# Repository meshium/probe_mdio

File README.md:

The PROBE_MDIO project

This is the PROBE_MDIO, an essential hardware multitool for exploring the MMI bus.

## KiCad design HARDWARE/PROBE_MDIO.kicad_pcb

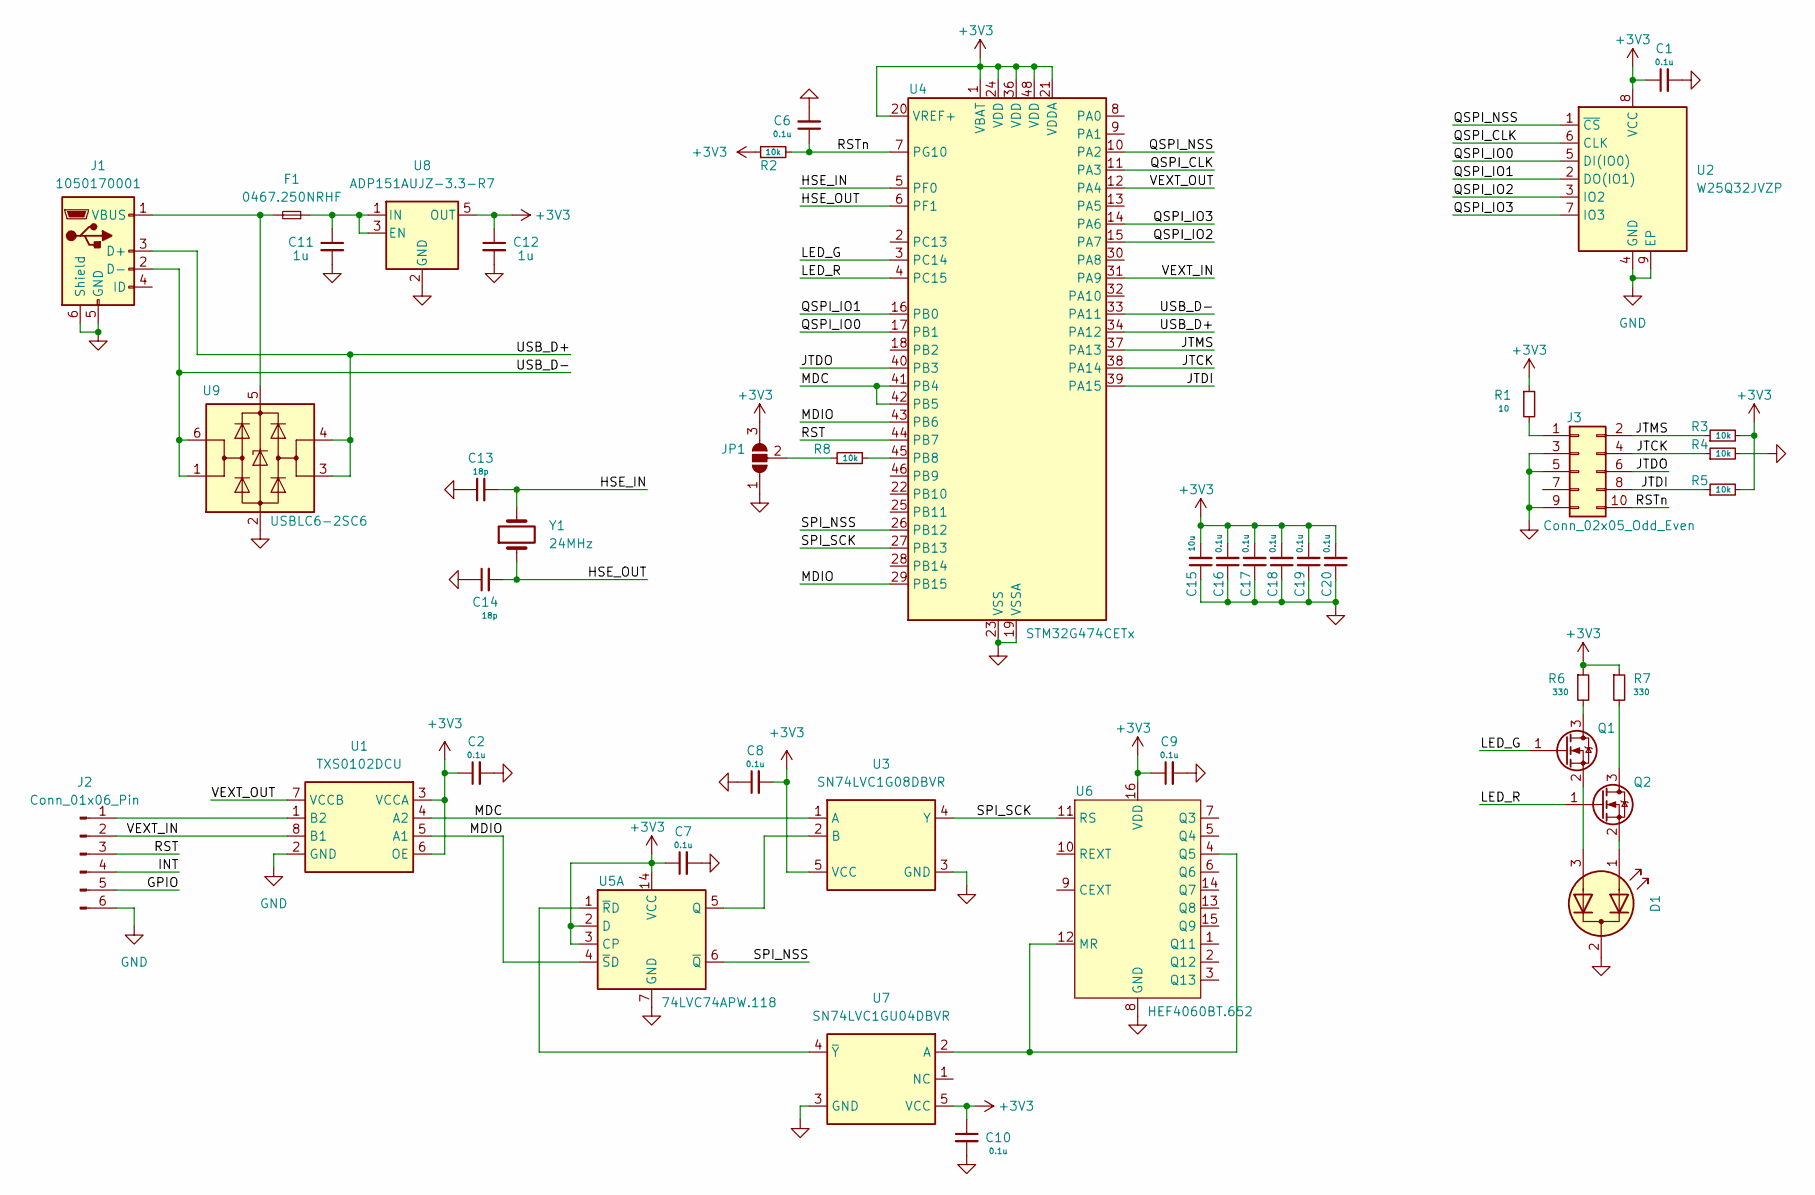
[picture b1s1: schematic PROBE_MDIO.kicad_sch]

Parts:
C1, C2, C6, C7, C8, C9, C10, C16, C17, C18, C19, C20: 0.1u; C_0402_1005Metric
C11, C12: 1u; C_0402_1005Metric
C13, C14: 18p; C_0402_1005Metric
C15: 10u; C_0603_1608Metric
D1: LED_Dual_AAK; LED_D3.0mm-3
F1: 0467.250NRHF; Fuse_0603_1608Metric
J1: 1050170001; USB_Micro-B_Molex-105017-0001
J2: Conn_01x06_Pin; PinHeader_1x06_P2.54mm_Horizontal
J3: Conn_02x05_Odd_Even; PinHeader_2x05_P1.27mm_Vertical
JP1: SolderJumper_3_Open; SolderJumper-3_P2.0mm_Open_TrianglePad1.0x1.5mm_NumberLabels
Q1, Q2: 2N7002; SOT-23
R1: 10; R_0402_1005Metric
R2, R3, R4, R5, R8: 10k; R_0402_1005Metric
R6, R7: 330; R_0402_1005Metric
U1: TXS0102DCU; VSSOP-8_2.3x2mm_P0.5mm
U2: W25Q32JVZP; WSON-8-1EP_6x5mm_P1.27mm_EP3.4x4.3mm
U3: SN74LVC1G08DBVR; SOT-23-5
U4: STM32G474CETx; LQFP-48_7x7mm_P0.5mm
U5: 74LVC74APW.118; TSSOP-14_4.4x5mm_P0.65mm
U6: HEF4060BT.652; SO-16_3.9x9.9mm_P1.27mm
U7: SN74LVC1GU04DBVR; SOT-23-5
U8: ADP151AUJZ-3.3-R7; TSOT-23-5
U9: USBLC6-2SC6; SOT-23-6
Y1: 24MHz; Crystal_SMD_3225-4Pin_3.2x2.5mm

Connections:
+3V3: C1.1, C2.1, C7.1, C8.2, C9.1, C10.1, C12.1, C15.2, C16.2, C17.2, C18.2, C19.2, C20.2, JP1.3 (B), R1.1, R2.1, R3.2, R5.2, R6.1, R7.1, U1.3 (VCCA), U1.6 (OE), U2.8 (VCC), U3.5 (VCC), U4.1 (VBAT), U4.20 (VREF+), U4.21 (VDDA), U4.24 (VDD), U4.36 (VDD), U4.48 (VDD), U5.2 (D), U5.3 (CP), U5.14 (VCC), U6.16 (VDD), U7.5 (VCC), U8.5 (OUT)
/GPIO: J2.5
/HSE_IN: C13.2, U4.5 (PF0), Y1.3
/HSE_OUT: C14.2, U4.6 (PF1), Y1.1
/INT: J2.4
/JTCK: J3.4, R4.1, U4.38 (PA14)
/JTDI: J3.8, R5.1, U4.39 (PA15)
/JTDO: J3.6, U4.40 (PB3)
/JTMS: J3.2, R3.1, U4.37 (PA13)
/LED_G: Q1.1 (G), U4.3 (PC14)
/LED_R: Q2.1 (G), U4.4 (PC15)
/MDC: U1.4 (A2), U3.1 (A), U4.41 (PB4), U4.42 (PB5)
/MDIO: U1.5 (A1), U4.29 (PB15), U4.43 (PB6), U5.4 (~SD)
/QSPI_CLK: U2.6 (CLK), U4.11 (PA3)
/QSPI_IO0: U2.5 (DI(IO0)), U4.17 (PB1)
/QSPI_IO1: U2.2 (DO(IO1)), U4.16 (PB0)
/QSPI_IO2: U2.3 (IO2), U4.15 (PA7)
/QSPI_IO3: U2.7 (IO3), U4.14 (PA6)
/QSPI_NSS: U2.1 (~CS), U4.10 (PA2)
/RST: J2.3, U4.44 (PB7)
/RSTn: C6.1, J3.10, R2.2, U4.7 (PG10)
/SPI_NSS: U4.26 (PB12), U5.6 (~Q)
/SPI_SCK: U3.4 (Y), U4.27 (PB13), U6.11 (RS)
/USB_D+: J1.3 (D+), U4.34 (PA12), U9.3 (I/O2), U9.4 (I/O2)
/USB_D-: J1.2 (D-), U4.33 (PA11), U9.1 (I/O1), U9.6 (I/O1)
/VEXT_IN: J2.2, U1.8 (B1), U4.31 (PA9)
/VEXT_OUT: U1.7 (VCCB), U4.12 (PA4)
GND: C1.2, C2.2, C6.2, C7.2, C8.1, C9.2, C10.2, C11.2, C12.2, C13.1, C14.1, C15.1, C16.1, C17.1, C18.1, C19.1, C20.1, D1.2 (K), J1.5 (GND), J1.6 (Shield), J2.6, J3.3, J3.5, J3.9, JP1.1 (A), R4.2, U1.2 (GND), U2.4 (GND), U2.9 (EP), U3.3 (GND), U4.19 (VSSA), U4.23 (VSS), U4.35 (VSS), U4.47 (VSS), U5.7 (GND), U6.8 (GND), U7.3 (GND), U8.2 (GND), U9.2 (GND)
unnamed: D1.1 (A1), Q2.2 (S)
unnamed: D1.3 (A2), Q1.2 (S)
unnamed: F1.2, J1.1 (VBUS), U9.5 (VBUS)
unnamed: J2.1, U1.1 (B2)
unnamed: J3.1, R1.2
unnamed: JP1.2 (C), R8.1
unnamed: Q1.3 (D), R6.2
unnamed: Q2.3 (D), R7.2
unnamed: U3.2 (B), U5.5 (Q)
unnamed: R8.2, U4.45 (PB8)
unnamed: U5.1 (~RD), U7.4 (~Y)
unnamed: U6.4 (Q5), U6.12 (MR), U7.2 (A)
unnamed: C11.1, F1.1, U8.1 (IN), U8.3 (EN)

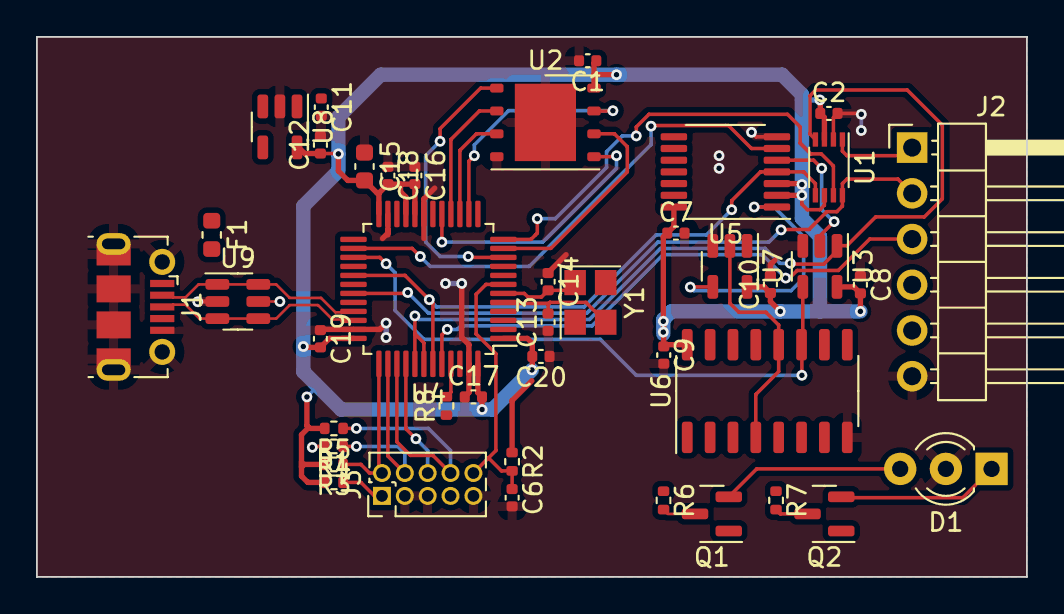
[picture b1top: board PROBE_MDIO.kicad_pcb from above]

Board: 2 copper layers, 55.0 x 30.0 mm, 43 parts (1 on the bottom side), 39 nets.

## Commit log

2023-08-30 Added pcb layout
